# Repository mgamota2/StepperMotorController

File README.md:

# Stepper Motor Controller

## Purpose

This project was designed for the EV Concept Car team to enable autonomous steering. Stepper motors provide precise rotation and high torque, making them perfect for turning a steering wheel.

## Design

This project is a 48V isolated stepper motor controller which can be controlled over CAN or USB. The MCU used for this project is the STM32F103C8T6. The foundational part of the design are the 2 isolated H-Bridge circuits which drive the two coils in the stepper motor. The PCB files, gerbers, and BOM are included in this repo.

## Sources

Thank you to Nefastor Online for the COM over USB library for the STM32F1:
https://nefastor.com/microcontrollers/stm32/usb/stm32cube-usb-device-library/cdc-continued/
https://github.com/Nefastor-Online/STM32_VCP.git

## Report

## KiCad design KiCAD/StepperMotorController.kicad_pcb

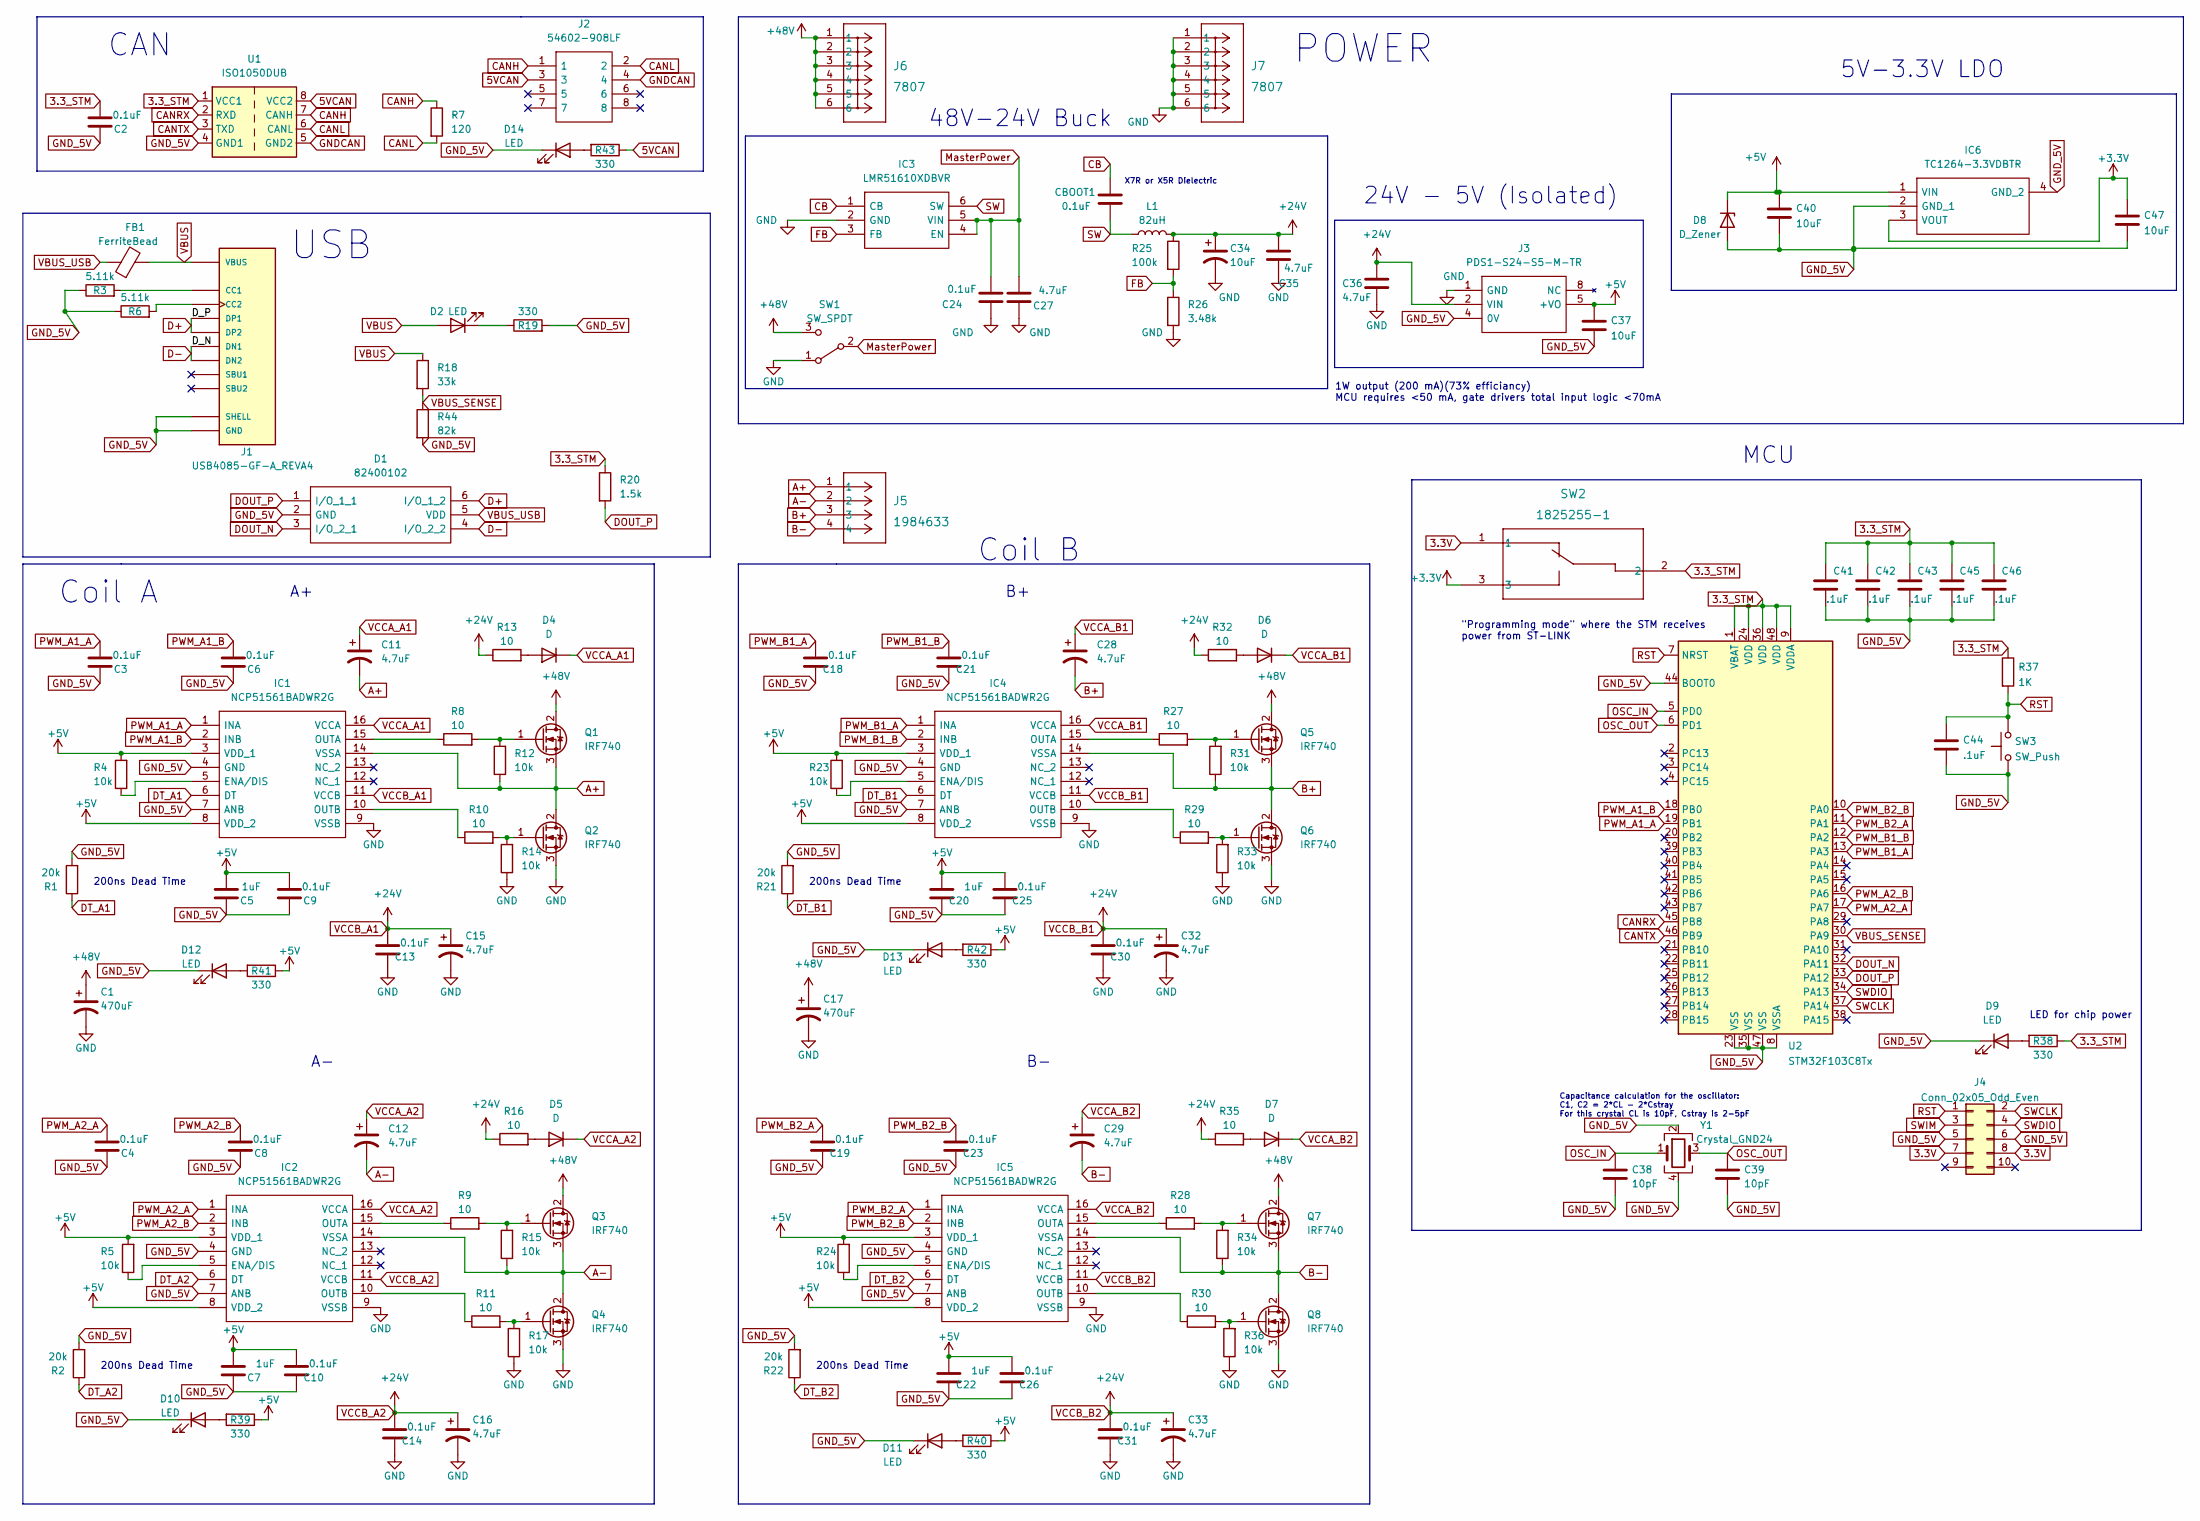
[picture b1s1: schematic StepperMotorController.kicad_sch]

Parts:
C1, C17: 470uF; CP_Radial_D16.0mm_P7.50mm
C2, C3, C4, C6, C8, C9, C10, C13, C14, C18, C19, C21, C23, C24, C25, C26, C30, C31: 0.1uF; C_0805_2012Metric
C5, C7, C20, C22: 1uF; C_0805_2012Metric
C11, C12, C15, C16, C28, C29, C32, C33: 4.7uF; CP_Radial_D8.0mm_P5.00mm
C27, C35, C36: 4.7uF; C_0805_2012Metric
C34, C37, C40, C47: 10uF; C_0805_2012Metric
C38, C39: 10pF; C_0603_1608Metric
C41, C42, C43, C44, C45, C46: .1uF; C_0805_2012Metric
CBOOT1: 0.1uF; C_0805_2012Metric
D1: 82400102; SOT95P280X145-6N; Mouser Part Number 710-82400102
D2, D9, D10, D11, D12, D13, D14: LED; LED_0603_1608Metric
D4, D5, D6, D7: D; D_0805_2012Metric
D8: D_Zener; D_0805_2012Metric
FB1: FerriteBead; R_0805_2012Metric
IC1, IC2, IC4, IC5: NCP51561BADWR2G; SOIC127P1030X265-16N; Manufacturer_Part_Number NCP51561BADWR2G
IC3: LMR51610XDBVR; SOT95P280X145-6N; Mouser Part Number 595-LMR51610XDBVR
IC6: TC1264-3.3VDBTR; SOT230P700X180-4N; Mouser Part Number 579-TC1264-3.3VDBTR
J1: USB4085-GF-A_REVA4; USB_C_Receptacle_GCT_USB4085; PARTREV A4
J2: 54602-908LF; 54602908LF; Mouser Part Number 649-54602-908LF
J3: PDS1-S24-S5-M-TR; PDS1S24S5MTR; Mouser Part Number 490-PDS1-S24-S5-M-TR
J4: Conn_02x05_Odd_Even; PinSocket_2x05_P2.54mm_Vertical
J5: 1984633; PhoenixContact_GMSTBVA_2,5_4-G-7,62_1x04_P7.62mm_Vertical
J6, J7: 7807; CONN_7807_KEY
L1: 82uH; L_Bourns_SRR1260
Q1, Q2, Q3, Q4, Q5, Q6, Q7, Q8: IRF740; TO-220-3_Vertical
R1, R2, R21, R22: 20k; R_0805_2012Metric
R3, R6: 5.11k; R_0805_2012Metric
R4, R5, R12, R14, R15, R17, R23, R24, R31, R33, R34, R36: 10k; R_0805_2012Metric
R7: 120; R_0805_2012Metric
R8, R9, R10, R11, R13, R16, R27, R28, R29, R30, R32, R35: 10; R_0805_2012Metric
R18: 33k; R_0805_2012Metric
R19, R38, R39, R40, R41, R42, R43: 330; R_0805_2012Metric
R20: 1.5k; R_0805_2012Metric
R25: 100k; R_0805_2012Metric
R26: 3.48k; R_0805_2012Metric
R37: 1K; R_0805_2012Metric
R44: 82k; R_0805_2012Metric
SW1: SW_SPDT; 100SP1T1_EWI
SW2: 1825255-1; SW3_1825255-1_TEC
SW3: SW_Push; SW_Push_SPST_NO_Alps_SKRK
U1: ISO1050DUB; SOP-8_6.62x9.15mm_P2.54mm
U2: STM32F103C8Tx; LQFP-48_7x7mm_P0.5mm
Y1: Crystal_GND24; ECS801033CHNTR3

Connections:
3.3V: J4.7, J4.8, SW2.1
3.3_STM: C2.2, C41.1, C42.1, C43.1, C45.1, C46.1, R20.1, R37.1, R38.1, SW2.2, U1.1 (VCC1), U2.1 (VBAT), U2.9 (VDDA), U2.24 (VDD), U2.36 (VDD), U2.48 (VDD)
5VCAN: J2.3, R43.1, U1.8 (VCC2)
+3.3V: C47.1, IC6.3 (VOUT), SW2.3
+5V: C5.2, C7.2, C9.2, C10.2, C20.2, C22.2, C25.2, C26.2, C37.1, C40.1, D8.1 (K), IC1.3 (VDD_1), IC1.8 (VDD_2), IC2.3 (VDD_1), IC2.8 (VDD_2), IC4.3 (VDD_1), IC4.8 (VDD_2), IC5.3 (VDD_1), IC5.8 (VDD_2), IC6.1 (VIN), J3.5 (+VO), R4.2, R5.2, R23.2, R24.2, R39.1, R40.1, R41.1, R42.1
+48V: C1.1, C17.1, J6.1, J6.2, J6.3, J6.4, J6.5, J6.6, Q1.2 (D), Q3.2 (D), Q5.2 (D), Q7.2 (D), SW1.3 (C)
A+: C11.2, IC1.14 (VSSA), J5.1, Q1.3 (S), Q2.2 (D), R12.1
A-: C12.2, IC2.14 (VSSA), J5.2, Q3.3 (S), Q4.2 (D), R15.1
B+: C28.2, IC4.14 (VSSA), J5.3, Q5.3 (S), Q6.2 (D), R31.1
B-: C29.2, IC5.14 (VSSA), J5.4, Q7.3 (S), Q8.2 (D), R34.1
CANH: J2.1, R7.1, U1.7 (CANH)
CANL: J2.2, R7.2, U1.6 (CANL)
CANRX: U1.2 (RXD), U2.45 (PB8)
CANTX: U1.3 (TXD), U2.46 (PB9)
CB: CBOOT1.1, IC3.1 (CB)
D+: D1.6 (I/O_1_2), J1.A6 (DP1), J1.B6 (DP2)
D-: D1.4 (I/O_2_2), J1.A7 (DN1), J1.B7 (DN2)
DOUT_N: D1.3 (I/O_2_1), U2.32 (PA11)
DOUT_P: D1.1 (I/O_1_1), R20.2, U2.33 (PA12)
DT_A1: IC1.6 (DT), R1.1
DT_A2: IC2.6 (DT), R2.1
DT_B1: IC4.6 (DT), R21.1
DT_B2: IC5.6 (DT), R22.1
FB: IC3.3 (FB), R25.2, R26.1
GND: C1.2, C13.1, C14.1, C15.2, C16.2, C17.2, C24.1, C27.1, C30.1, C31.1, C32.2, C33.2, C34.2, C35.1, C36.2, IC1.9 (VSSB), IC2.9 (VSSB), IC3.2 (GND), IC4.9 (VSSB), IC5.9 (VSSB), J3.1 (GND), J7.1, J7.2, J7.3, J7.4, J7.5, J7.6, Q2.3 (S), Q4.3 (S), Q6.3 (S), Q8.3 (S), R14.1, R17.1, R26.2, R33.1, R36.1, SW1.1 (A)
GNDCAN: J2.4, U1.5 (GND2)
GND_5V: C2.1, C3.1, C4.1, C5.1, C6.1, C7.1, C8.1, C9.1, C10.1, C18.1, C19.1, C20.1, C21.1, C22.1, C23.1, C25.1, C26.1, C37.2, C38.2, C39.2, C40.2, C41.2, C42.2, C43.2, C44.2, C45.2, C46.2, C47.2, D1.2 (GND), D8.2 (A), D9.1 (K), D10.1 (K), D11.1 (K), D12.1 (K), D13.1 (K), D14.1 (K), IC1.4 (GND), IC1.7 (ANB), IC2.4 (GND), IC2.7 (ANB), IC4.4 (GND), IC4.7 (ANB), IC5.4 (GND), IC5.7 (ANB), IC6.2 (GND_1), IC6.4 (GND_2), J1.A1 (GND), J1.A12 (GND), J1.B1 (GND), J1.B12 (GND), J1.P1 (SHELL), J1.P2 (SHELL), J1.P3 (SHELL), J1.P4 (SHELL), J3.4 (0V), J4.5, J4.6, R1.2, R2.2, R3.1, R6.1, R19.2, R21.2, R22.2, R44.2, SW3.1, U1.4 (GND1), U2.8 (VSSA), U2.23 (VSS), U2.35 (VSS), U2.44 (BOOT0), U2.47 (VSS), Y1.2, Y1.4; also elsewhere on the board
MasterPower: C24.2, C27.2, IC3.4 (EN), IC3.5 (VIN), SW1.2 (B)
unnamed 28: D2.1 (K), R19.1; also elsewhere on the board
unnamed: D4.2 (A), R13.2
unnamed: D5.2 (A), R16.2
unnamed: D6.2 (A), R32.2
unnamed: D7.2 (A), R35.2
unnamed 33: D9.2 (A), R38.2; also elsewhere on the board
unnamed: D10.2 (A), R39.2
unnamed: D11.2 (A), R40.2
unnamed: D12.2 (A), R41.2
unnamed: D13.2 (A), R42.2
unnamed: D14.2 (A), R43.2
unnamed: IC1.5 (ENA/DIS), R4.1
unnamed: IC1.10 (OUTB), R10.1
unnamed: IC1.15 (OUTA), R8.1
unnamed: IC2.5 (ENA/DIS), R5.1
unnamed: IC2.10 (OUTB), R11.1
unnamed: IC2.15 (OUTA), R9.1
unnamed: IC4.5 (ENA/DIS), R23.1
unnamed: IC4.10 (OUTB), R29.1
unnamed: IC4.15 (OUTA), R27.1
unnamed: IC5.5 (ENA/DIS), R24.1
unnamed: IC5.10 (OUTB), R30.1
unnamed: IC5.15 (OUTA), R28.1
unnamed: J1.A5 (CC1), R3.2
unnamed: J1.B5 (CC2), R6.2
unnamed: Q1.1 (G), R8.2, R12.2
unnamed: Q2.1 (G), R10.2, R14.2
unnamed: Q3.1 (G), R9.2, R15.2
unnamed: Q4.1 (G), R11.2, R17.2
unnamed: Q5.1 (G), R27.2, R31.2
unnamed: Q6.1 (G), R29.2, R33.2
unnamed: Q7.1 (G), R28.2, R34.2
unnamed: Q8.1 (G), R30.2, R36.2
OSC_IN: C38.1, U2.5 (PD0), Y1.1
OSC_OUT: C39.1, U2.6 (PD1), Y1.3
PWM_A1_A: C3.2, IC1.1 (INA), U2.19 (PB1)
PWM_A1_B: C6.2, IC1.2 (INB), U2.18 (PB0)
PWM_A2_A: C4.2, IC2.1 (INA), U2.17 (PA7)
PWM_A2_B: C8.2, IC2.2 (INB), U2.16 (PA6)
PWM_B1_A: C18.2, IC4.1 (INA), U2.13 (PA3)
PWM_B1_B: C21.2, IC4.2 (INB), U2.12 (PA2)
PWM_B2_A: C19.2, IC5.1 (INA), U2.11 (PA1)
PWM_B2_B: C23.2, IC5.2 (INB), U2.10 (PA0)
RST: C44.1, J4.1, R37.2, SW3.2, U2.7 (NRST)
SW: CBOOT1.2, IC3.6 (SW), L1.1
SWCLK: J4.2, U2.37 (PA14)
SWDIO: J4.4, U2.34 (PA13)
SWIM: J4.3
VBUS: D2.2 (A), FB1.2, J1.A4 (VBUS), J1.A9 (VBUS), J1.B4 (VBUS), J1.B9 (VBUS), R18.1; also elsewhere on the board
VBUS_SENSE: R18.2, R44.1, U2.30 (PA9)
VBUS_USB: D1.5 (VDD), FB1.1
VCCA_A1: C11.1, D4.1 (K), IC1.16 (VCCA)
VCCA_A2: C12.1, D5.1 (K), IC2.16 (VCCA)
VCCA_B1: C28.1, D6.1 (K), IC4.16 (VCCA)
VCCA_B2: C29.1, D7.1 (K), IC5.16 (VCCA)
VCCB_A1: C13.2, C14.2, C15.1, C16.1, C30.2, C31.2, C32.1, C33.1, C34.1, C35.2, C36.1, IC1.11 (VCCB), IC2.11 (VCCB), IC4.11 (VCCB), IC5.11 (VCCB), J3.2 (VIN), L1.2, R13.1, R16.1, R25.1, R32.1, R35.1

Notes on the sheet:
X7R or X5R Dielectric
Capacitance calculation for the oscillator: C1, C2 = 2*CL - 2*Cstray For this crystal CL is 10pF, Cstray is 2-5pF
Coil B
1W output (200 mA)(73% efficiancy) MCU requires <50 mA, gate drivers total input logic <70mA
USB
MCU
200ns Dead Time
LED for chip power
CAN
24V - 5V (Isolated)
48V-24V Buck
Coil A
5V-3.3V LDO
POWER
"Programming mode" where the STM receives power from ST-LINK

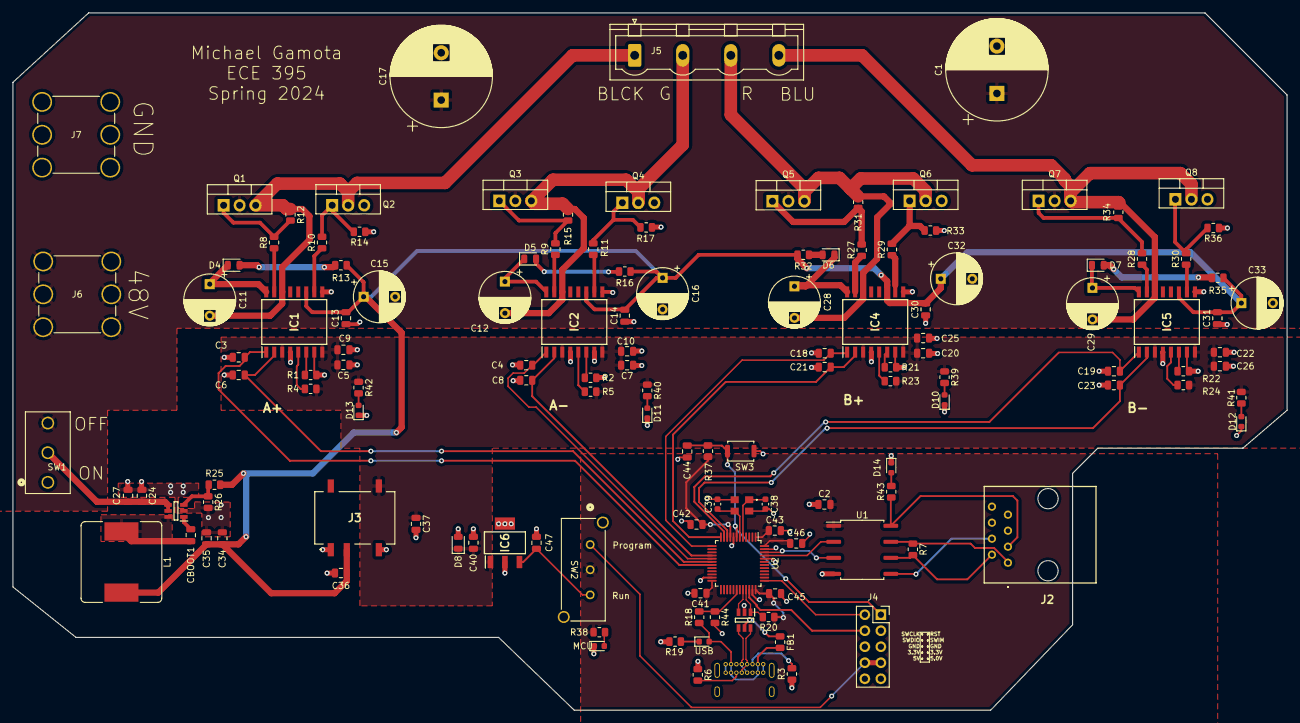
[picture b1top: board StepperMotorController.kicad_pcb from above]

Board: 2 copper layers, 202.0 x 110.6 mm, 134 parts (1 on the bottom side), 83 nets.

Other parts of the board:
MCU: LED; LED_0603_1608Metric
USB: LED; LED_0603_1608Metric

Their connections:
GND_5V: MCU.1 (K); also elsewhere on the board
unnamed 28: USB.1 (K); also elsewhere on the board
unnamed 33: MCU.2 (A); also elsewhere on the board
VBUS: USB.2 (A); also elsewhere on the board

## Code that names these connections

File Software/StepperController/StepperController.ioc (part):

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Mcu.Name=STM32F103C(8-B)Tx
Mcu.Package=LQFP48
Mcu.UserName=STM32F103C8Tx
PA0-WKUP.GPIOParameters=GPIO_Label
PA0-WKUP.GPIO_Label=PWM_B2B
PA0-WKUP.Signal=S_TIM2_CH1_ETR
PA1.GPIOParameters=GPIO_Label
PA1.GPIO_Label=PWM_B2A
PA1.Signal=S_TIM2_CH2
PA11.Mode=Device
PA11.Signal=USB_DM
PA12.Mode=Device
PA12.Signal=USB_DP
PA13.Mode=Serial_Wire
PA13.Signal=SYS_JTMS-SWDIO
PA14.Mode=Serial_Wire
PA14.Signal=SYS_JTCK-SWCLK
PA2.GPIOParameters=GPIO_Label
PA2.GPIO_Label=PWM_B1B
PA2.Signal=S_TIM2_CH3
PA3.GPIOParameters=GPIO_Label
PA3.GPIO_Label=PWM_B1A
PA3.Signal=S_TIM2_CH4
PA6.GPIOParameters=GPIO_Label
PA6.GPIO_Label=PWM_A2B
PA6.Signal=S_TIM3_CH1
PA7.GPIOParameters=GPIO_Label
PA7.GPIO_Label=PWM_A2A
PA7.Signal=S_TIM3_CH2
PB0.GPIOParameters=GPIO_Label
PB0.GPIO_Label=PWM_A1B
PB0.Signal=S_TIM3_CH3
PB1.GPIOParameters=GPIO_Label
PB1.GPIO_Label=PWM_A1A
PB1.Signal=S_TIM3_CH4
PB8.Mode=CAN_Activate
PB8.Signal=CAN_RX
PB9.Mode=CAN_Activate
PB9.Signal=CAN_TX
PD0-OSC_IN.Mode=HSE-External-Oscillator
PD0-OSC_IN.Signal=RCC_OSC_IN
PD1-OSC_OUT.Mode=HSE-External-Oscillator
PD1-OSC_OUT.Signal=RCC_OSC_OUT
RCC.SYSCLKFreq_VALUE=48000000
RCC.SYSCLKSource=RCC_SYSCLKSOURCE_PLLCLK
board=custom

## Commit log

2024-05-07 Adding report
2024-05-07 Report update
